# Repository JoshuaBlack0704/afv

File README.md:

Before attempting to learn how to use this codebase it is GREATLY recommended
to learn [Rust](https://www.rust-lang.org).
Once you have installed rust through [Rustup](https://rustup.rs) you can use `cargo doc --open` from within the gcs-afv folder to
view its documention. Same goes for afv-internal

It is highly recommended to familiarize yourself with the following crates:
* [Eframe](https://docs.rs/eframe/latest/eframe)
* [Retina](https://docs.rs/retina/latest/retina)
* [Tokio](https://docs.rs/tokio/latest/tokio)
* [Image](https://docs.rs/image/latest/image)

If you have any questions please feel free to reach me (Joshua Black) at:
* `Text`:  +1 417-848-8609
* `Email`: jtblack0704@gmail.com

At the end of your ownership of this codebase, please either delete my contact info or replace it with your own.

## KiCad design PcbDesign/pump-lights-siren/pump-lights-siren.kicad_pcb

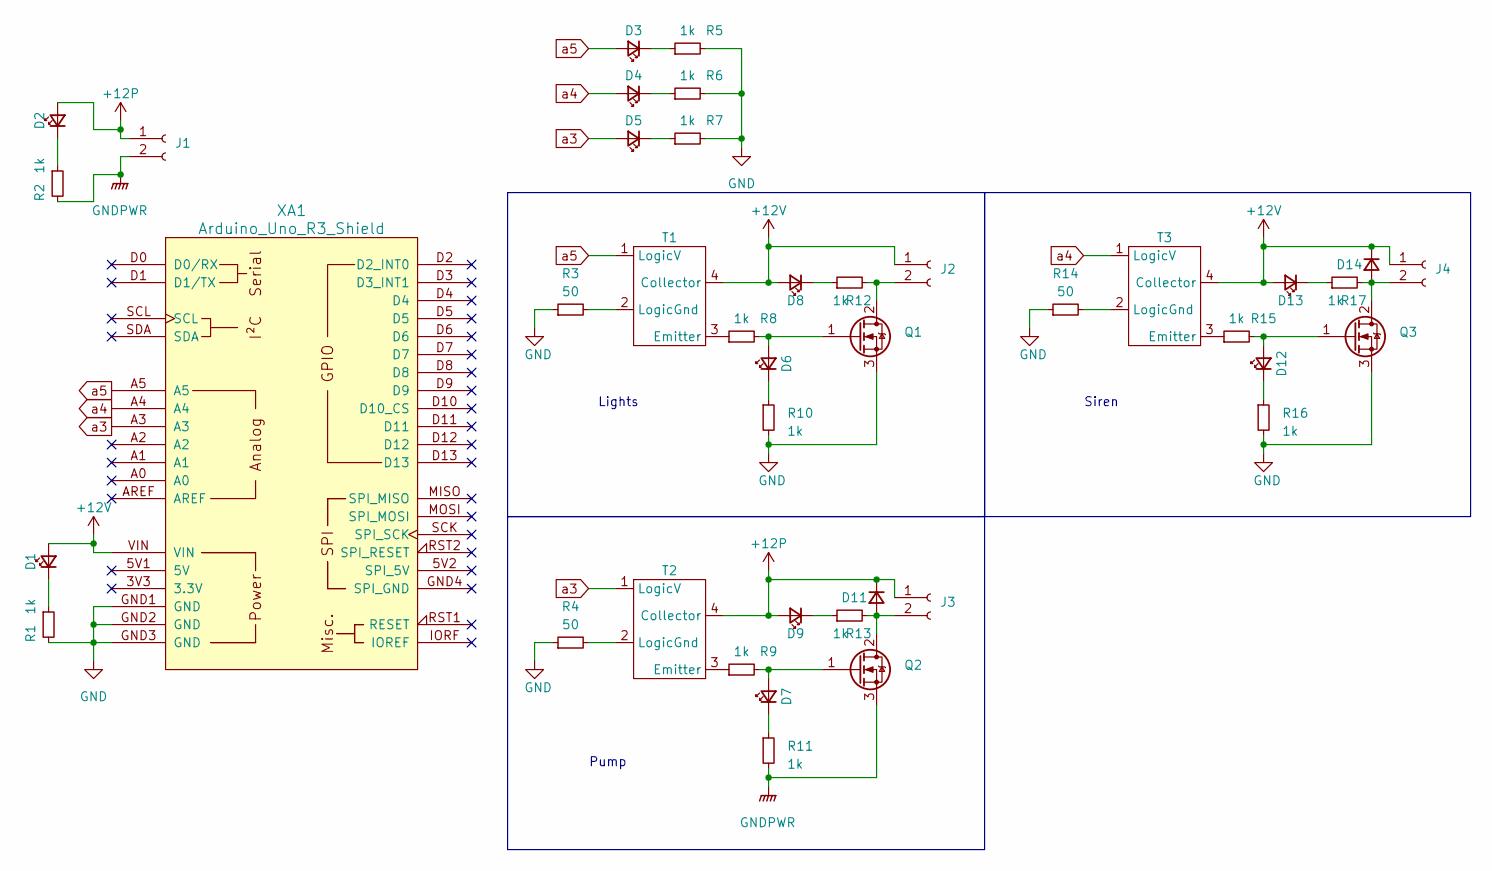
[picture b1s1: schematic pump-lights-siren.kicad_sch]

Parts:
D1, D2, D3, D4, D5, D6, D7, D8, D9, D12, D13: LED_Small; LED_0603_1608Metric_Pad1.05x0.95mm_HandSolder
D11, D14: D_Small; TO-220-2_Horizontal_TabDown
J1, J2, J3, J4: Conn_01x02_Socket; PhoenixContact_MC_1,5_2-G-3.5_1x02_P3.50mm_Horizontal
Q1, Q2, Q3: Q_NMOS_GDS; TO-220-3_Horizontal_TabDown
R1, R2, R5, R6, R7, R8, R9, R10, R11, R12, R13, R15, R16, R17: 1k; R_0603_1608Metric_Pad0.98x0.95mm_HandSolder
R3, R4, R14: 50; R_0603_1608Metric_Pad0.98x0.95mm_HandSolder
T1, T2, T3: DIP-4_W7.62mm
XA1: Arduino_Uno_R3_Shield

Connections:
+12P: D2.2 (A), D9.2 (A), D11.1 (K), J1.1, J3.1, T2.4 (Collector)
+12V: D1.2 (A), D8.2 (A), D13.2 (A), D14.1 (K), J2.1, J4.1, T1.4 (Collector), T3.4 (Collector), XA1.VIN
GND: Q1.3 (S), Q3.3 (S), R1.2, R3.1, R4.1, R5.2, R6.2, R7.2, R10.2, R14.1, R16.2, XA1.GND1 (GND), XA1.GND2 (GND), XA1.GND3 (GND)
GNDPWR: J1.2, Q2.3 (S), R2.2, R11.2
unnamed: D1.1 (K), R1.1
unnamed: D2.1 (K), R2.1
unnamed: D3.1 (K), R5.1
unnamed: D4.1 (K), R6.1
unnamed: D5.1 (K), R7.1
unnamed: D6.2 (A), Q1.1 (G), R8.2
unnamed: D6.1 (K), R10.1
unnamed: D7.2 (A), Q2.1 (G), R9.2
unnamed: D7.1 (K), R11.1
unnamed: D8.1 (K), R12.1
unnamed: D9.1 (K), R13.1
unnamed: D11.2 (A), J3.2, Q2.2 (D), R13.2
unnamed: D12.2 (A), Q3.1 (G), R15.2
unnamed: D12.1 (K), R16.1
unnamed: D13.1 (K), R17.1
unnamed: D14.2 (A), J4.2, Q3.2 (D), R17.2
unnamed: J2.2, Q1.2 (D), R12.2
unnamed: R8.1, T1.3 (Emitter)
unnamed: R3.2, T1.2 (LogicGnd)
unnamed: R9.1, T2.3 (Emitter)
unnamed: R4.2, T2.2 (LogicGnd)
unnamed: R15.1, T3.3 (Emitter)
unnamed: R14.2, T3.2 (LogicGnd)
a3: D5.2 (A), T2.1 (LogicV), XA1.A3
a4: D4.2 (A), T3.1 (LogicV), XA1.A4
a5: D3.2 (A), T1.1 (LogicV), XA1.A5

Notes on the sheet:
Siren
Pump
Lights

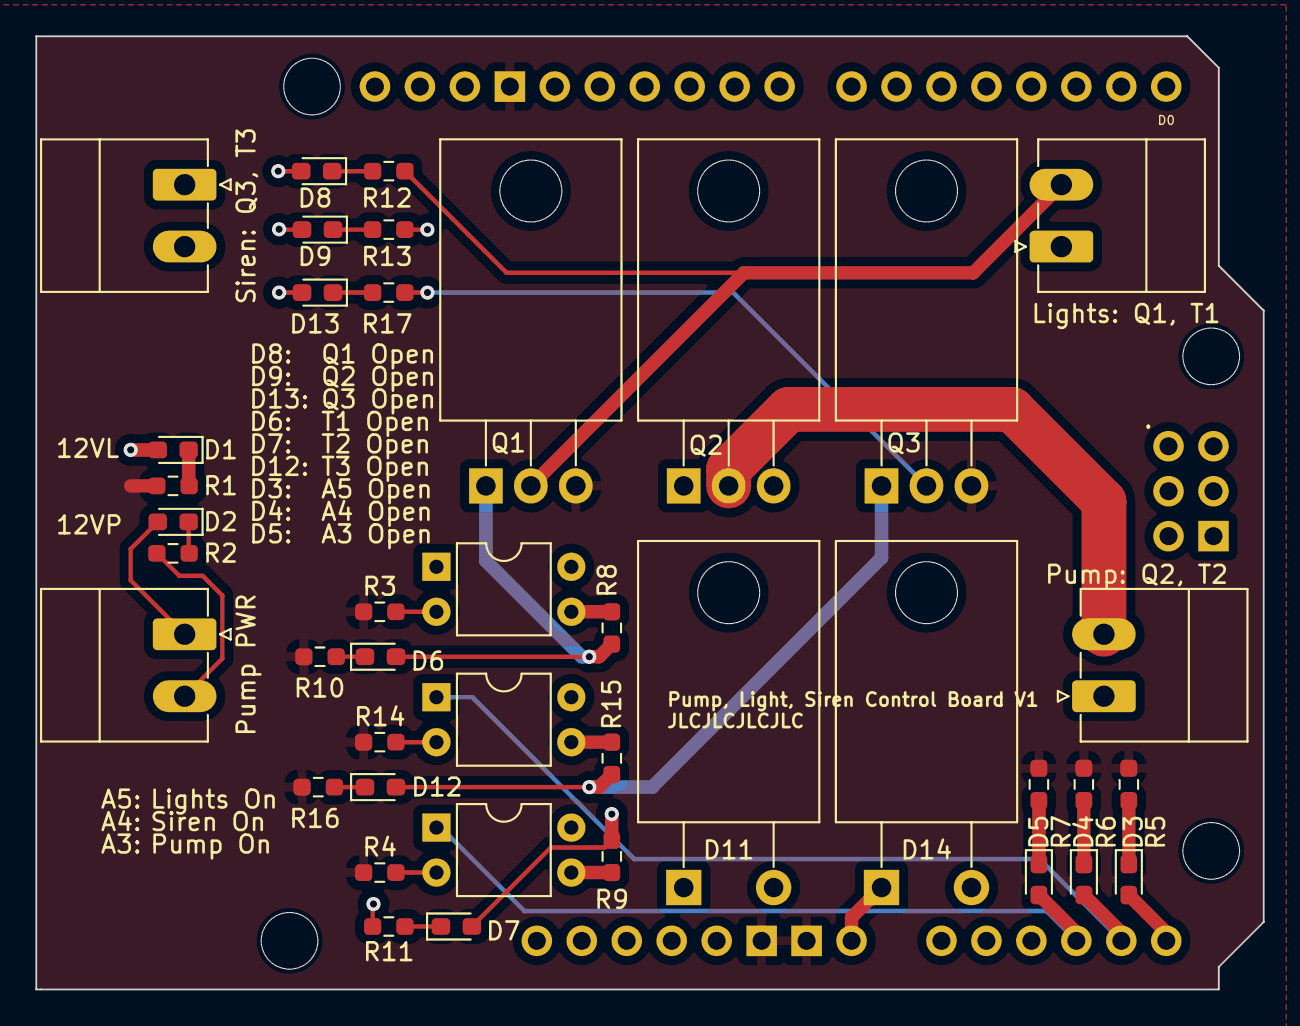
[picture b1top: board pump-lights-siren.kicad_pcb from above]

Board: 4 copper layers, 69.3 x 53.8 mm, 41 parts (0 on the bottom side), 30 nets.

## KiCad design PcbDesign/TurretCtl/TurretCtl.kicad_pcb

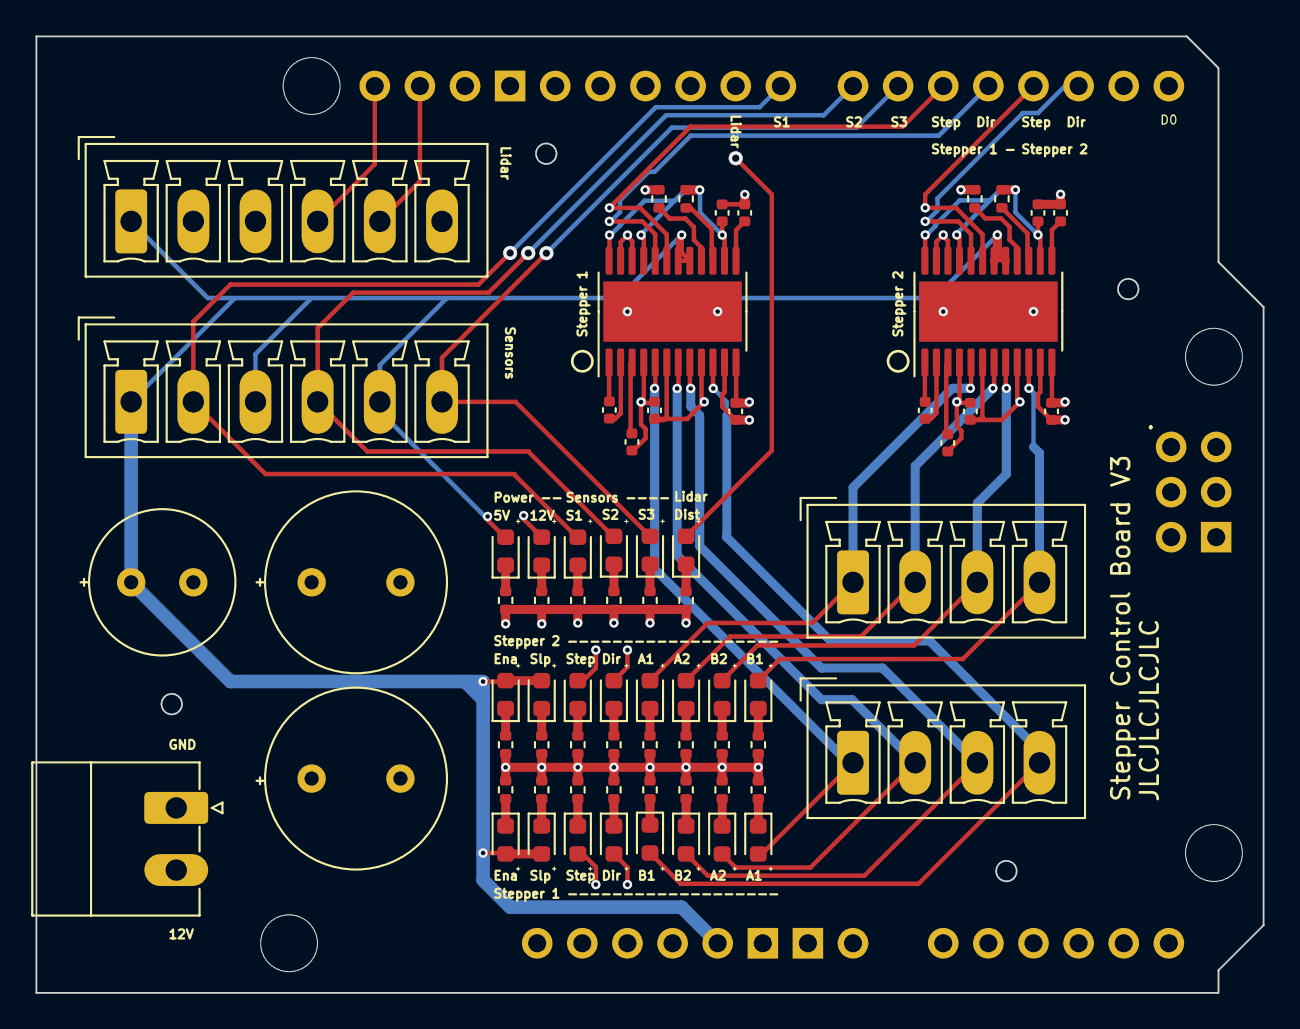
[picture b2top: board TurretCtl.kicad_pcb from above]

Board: 4 copper layers, 69.1 x 53.8 mm, 71 parts (0 on the bottom side), 57 nets.

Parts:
C1, C3: 22nF; C_0402_1005Metric
C2, C4: 220nF; C_0402_1005Metric
C5, C6, C10, C11: 10nF; C_0402_1005Metric
C7, C12: 150uf; C_Radial_D10.0mm_H12.5mm_P5.00mm
C8, C9, C13, C14: 470nF; C_0402_1005Metric
C15: 680uF; C_Radial_D8.0mm_H11.5mm_P3.50mm
D1, D2, D3, D4, D5, D6, D7, D8, D9, D10, D11, D12, D13, D14, D15, D16, D17, D18, D19, D20, D21, D22: LED; LED_0603_1608Metric
J1: FLIR; PhoenixContact_MCV_1,5_6-G-3.5_1x06_P3.50mm_Vertical
J2: Stepper1; PhoenixContact_MCV_1,5_4-G-3.5_1x04_P3.50mm_Vertical
J3: Stepper2; PhoenixContact_MCV_1,5_4-G-3.5_1x04_P3.50mm_Vertical
J4: PWR; PhoenixContact_MC_1,5_2-G-3.5_1x02_P3.50mm_Horizontal
J5: Sensors; PhoenixContact_MCV_1,5_6-G-3.5_1x06_P3.50mm_Vertical
R1, R4: 30k; R_0402_1005Metric
R2, R3: 10k; R_0402_1005Metric
R5, R6, R7, R8, R9, R10, R11, R12, R13, R14, R15, R16, R17, R18, R19, R20, R21, R22, R23, R24, R25, R26: 330; R_0402_1005Metric
U1, U2: HTSSOP-24-1EP_4.4x7.8mm_P0.65mm_EP3.4x7.8mm_Mask2.4x2.98mm
XA1: Arduino_Uno_R3_Shield

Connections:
+5V: C15.1, D12.2 (A), D13.2 (A), D14.2 (A), D16.2 (A), D17.2 (A), J1.1, J5.1, J5.3, J5.5, U1.17 (nSLEEP), U1.18 (ENABLE), U2.17 (nSLEEP), U2.18 (ENABLE), XA1.5V1 (5V)
+12V: C2.1, C4.1, C5.1, C6.1, C7.1, C10.1, C11.1, C12.1, D1.2 (A), J4.2, U1.4 (VM), U1.11 (VM), U2.4 (VM), U2.11 (VM), XA1.VIN
/Stepper1/AVDD: C9.1, U2.13 (AVDD)
/Stepper1/CPH: C3.1, U2.2 (CPH)
/Stepper1/CPL: C3.2, U2.1 (CPL)
/Stepper1/DVDD: C8.1, R2.1, U2.14 (DVDD), U2.21 (M0), U2.24 (DECAY)
/Stepper1/RREF: R1.1, U2.16 (RREF)
/Stepper1/VCP: C4.2, U2.3 (VCP)
/Stepper1/nFAULT: R2.2, U2.15 (nFAULT)
/Stepper2/AVDD: C14.1, U1.13 (AVDD)
/Stepper2/CPH: C1.1, U1.2 (CPH)
/Stepper2/CPL: C1.2, U1.1 (CPL)
/Stepper2/DVDD: C13.1, R3.1, U1.14 (DVDD), U1.21 (M0), U1.24 (DECAY)
/Stepper2/RREF: R4.1, U1.16 (RREF)
/Stepper2/VCP: C2.2, U1.3 (VCP)
/Stepper2/nFAULT: R3.2, U1.15 (nFAULT)
D6: D15.2 (A), J5.6, XA1.D6
D7: D18.2 (A), J5.4, XA1.D7
D8: D19.2 (A), J5.2, XA1.D8
GND: C5.2, C6.2, C7.2, C8.2, C9.2, C10.2, C11.2, C12.2, C13.2, C14.2, C15.2, J1.6, J4.1, R1.2, R4.2, R5.2, R6.2, R7.2, R8.2, R9.2, R10.2, R11.2, R12.2, R13.2, R14.2, R15.2, R16.2, R17.2, R18.2, R19.2, R20.2, R21.2, R22.2, R23.2, R24.2, R25.2, R26.2, U1.6 (PGND), U1.9 (PGND), U1.12 (GND), U1.22 (M1), U1.23 (TRQ), U2.6 (PGND), U2.9 (PGND), U2.12 (GND), U2.22 (M1), U2.23 (TRQ), XA1.GND1 (GND), XA1.GND2 (GND), XA1.GND3 (GND)
unnamed: D1.1 (K), R5.1
unnamed: D2.1 (K), R6.1
unnamed: D3.1 (K), R7.1
unnamed: D4.1 (K), R8.1
unnamed: D5.1 (K), R9.1
unnamed: D6.1 (K), R10.1
unnamed: D7.1 (K), R11.1
unnamed: D8.1 (K), R12.1
unnamed: D9.1 (K), R13.1
unnamed: D10.2 (A), XA1.D9
unnamed: D10.1 (K), R14.1
unnamed: D11.1 (K), R15.1
unnamed: D12.1 (K), R16.1
unnamed: D13.1 (K), R17.1
unnamed: D14.1 (K), R18.1
unnamed: D15.1 (K), R19.1
unnamed: D16.1 (K), R20.1
unnamed: D17.1 (K), R21.1
unnamed: D18.1 (K), R22.1
unnamed: D19.1 (K), R23.1
unnamed: D20.1 (K), R24.1
unnamed: D21.1 (K), R25.1
unnamed: D22.1 (K), R26.1
S1_AOUT1: D8.2 (A), J2.1, U2.5 (AOUT1)
S1_AOUT2: D6.2 (A), J2.2, U2.7 (AOUT2)
S1_BOUT1: D2.2 (A), J2.4, U2.10 (BOUT1)
S1_BOUT2: D4.2 (A), J2.3, U2.8 (BOUT2)
S1_DIR: D22.2 (A), U2.20 (DIR), XA1.D4
S1_STEP: D21.2 (A), U2.19 (STEP), XA1.D5
S2_AOUT1: D9.2 (A), J3.1, U1.5 (AOUT1)
S2_AOUT2: D7.2 (A), J3.2, U1.7 (AOUT2)
S2_BOUT1: D3.2 (A), J3.4, U1.10 (BOUT1)
S2_BOUT2: D5.2 (A), J3.3, U1.8 (BOUT2)
S2_DIR: D20.2 (A), U1.20 (DIR), XA1.D2 (D2_INT0)
S2_STEP: D11.2 (A), U1.19 (STEP), XA1.D3 (D3_INT1)
SCL: J1.4, XA1.SCL
SDA: J1.5, XA1.SDA

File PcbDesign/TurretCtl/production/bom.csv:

Designator,Footprint,Quantity,Value,LCSC Part #
"C1, C3",0402,2,22nF,C1532
"C10, C11, C5, C6",0402,4,10nF,C15195
"C12, C7",C_Radial_D10.0mm_H12.5mm_P5.00mm,2,150uf,C432404
"C13, C14, C8, C9",0402,4,470nF,C437526
C15,C_Radial_D8.0mm_H11.5mm_P3.50mm,1,680uF,C88760
"C2, C4",0402,2,220nF,C16772
"D1, D10, D11, D12, D13, D14, D15, D16, D17, D18, D19, D2, D20, D21, D22, D3, D4, D5, D6, D7, D8, D9",0603,22,LED,C2286
J1,"PhoenixContact_MCV_1,5_6-G-3.5_1x06_P3.50mm_Vertical",1,FLIR,C133065
J2,"PhoenixContact_MCV_1,5_4-G-3.5_1x04_P3.50mm_Vertical",1,Stepper1,
J3,"PhoenixContact_MCV_1,5_4-G-3.5_1x04_P3.50mm_Vertical",1,Stepper2,
J4,"PhoenixContact_MC_1,5_2-G-3.5_1x02_P3.50mm_Horizontal",1,PWR,
J5,"PhoenixContact_MCV_1,5_6-G-3.5_1x06_P3.50mm_Vertical",1,Sensors,C133065
"R1, R4",0402,2,30k,C25779
"R10, R11, R12, R13, R14, R15, R16, R17, R18, R19, R20, R21, R22, R23, R24, R25, R26, R5, R6, R7, R8, R9",0402,22,330,C25104
"R2, R3",0402,2,10k,C25744
"U1, U2",HTSSOP-24-1EP_4.4x7.8mm_P0.65mm_EP3.4x7.8mm_Mask2.4x2.98mm,2,~,
XA1,Arduino_Uno_R3_Shield,1,Arduino_Uno_R3_Shield,

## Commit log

2023-01-20 Bits struct
2023-01-23 Attempting Ethernet Shield
2023-01-23 Delays and 16bit addr
2023-01-23 addr
2023-01-23 Working communication with w5500
2023-01-24 Registers
2023-01-27 FLIR RTSP image retrieval
2023-01-30 Working Flir gui pipeline
2023-01-30 Bug fixing h.264
2023-01-30 Testing nal splitting
2023-01-30 Successfully retreived flir image
2023-01-31 Grayscale image analysis
2023-02-01 Working median analysis
2023-02-02 Started network
2023-02-02 Ethernet testing
2023-02-02 Working ethernet bus
2023-02-03 Ip scanner gui work
2023-02-03 Working ip scanner
2023-02-03 Scanner optimizations
2023-02-04 Starting ctl system
2023-02-06 AfvCtl contacting dummy afv
2023-02-06 Flir processing deps
2023-02-06 New flir implementation
2023-02-06 RTSP stream
2023-02-06 Live rtsp stream
2023-02-06 Removed outdated crates
2023-02-06 Working on A50link
2023-02-07 Will switch to Feed api
2023-02-07 Actuator/Link api
2023-02-08 No rt scanner
2023-02-08 Flir search for actuator
2023-02-08 Link ready for test
2023-02-09 Working flir stream and control
2023-02-09 Turret system simulation
2023-02-13 Turret work
2023-02-13 Scanner update
2023-02-13 Interface scanning
2023-02-14 Turret v2 scaffolding
2023-02-14 Starting turret two comtrollers
2023-02-14 Working Turret V2
2023-02-15 Servo ctl
2023-02-15 w5500
2023-02-16 Working Servo Control
2023-02-16 Timer1 interrupts
2023-02-17 Testing w5500
2023-02-17 Starting w5500 driver
2023-02-17 w5500 Register work
2023-02-18 Socket register work
2023-02-20 Socker register work
2023-02-20 Successful one way coms to the mcu!
2023-02-20 Removed old clutter
2023-02-20 MainCtl mcu process
2023-02-20 Full duplex coms through w5500
2023-02-20 Bug fixing
2023-02-24 Started general bus
2023-02-27 TurretCtl Pcb
2023-02-28 TurretCtl revision
2023-02-28 TurretCtl V0.1
2023-02-28 Started gcs bus design
2023-03-01 Gui for bus
2023-03-01 TurretCtl V2
2023-03-01 Foot print selection
2023-03-02 Reader for JLCPCB run
2023-03-02 New Backup
2023-03-03 Bus work
2023-03-04 Successful network comms
2023-03-04 Afv Control
2023-03-05 Afv monolith
2023-03-06 Flir system started
2023-03-07 Flir Testing
2023-03-07 Re-Implemented flir system with naive target setter
2023-03-07 Standalone flir ops
2023-03-08 Auto Targeting system
2023-03-09 Monolith TargetingComputer
2023-03-11 Auto target pathway
2023-03-21 Removed redundant library code
2023-03-22 Working auto reconnecting socket system
2023-03-22 Scan and connect to flir turret
2023-03-25 Stepper Control Board V2
2023-03-25 Removed dvdd leds
2023-04-12 New connectors
2023-04-12 New Layout
2023-04-12 Control board v3
2023-04-12 V3 adjustments
2023-04-12 ping steppers
2023-04-13 Systemd start
2023-04-13 Systemd start fixes
2023-04-13 Basic stepper driver
2023-04-13 Pan tilt test ethernet
2023-04-18 PCB changes
2023-04-18 Scaffolding
2023-04-18 Working on afv bridge
2023-04-18 Successful connection
2023-04-18 Afvs are selectable
2023-04-19 Communication
2023-04-19 Opto transistors
2023-04-19 Mosfet design
2023-04-20 Flir streaming
2023-04-21 Can now command turret after analysis
2023-04-21 Arduino turret driver
2023-04-22 Working cross talk
2023-04-22 Auto connect issues resolved
2023-04-23 Turret driver operational when compoling mcu code with release flag
2023-04-23 Lidar driver network connection
2023-04-23 Untested garmin lidar driver
2023-04-24 Pump Lights and Sirens drivers communicating
2023-04-24 Flash memory limitation on Arduino
2023-04-25 Tilt auto target
2023-04-25 Updated service
2023-04-27 Routing Error
2023-04-27 Auto targeting timing code rewritten
2023-04-27 Testing
2023-04-27 Working system
2023-04-28 Pump
2023-05-01 Speed fest snap changes
2023-05-11 docs
2023-05-12 Finished basic docs
2023-05-12 Readme
2023-05-12 Cap error
2023-05-12 Run commands
2023-05-12 Readme changes
